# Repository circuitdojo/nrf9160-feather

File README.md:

# Circuit Dojo - nRF9160 Feather Hardware Files

## Purchase

Considering supporting the project and purchasing a nRF9160 Feather at the following locations:

1. [The Circuit Dojo Official Store](https://www.circuitdojo.com/products/nrf9160-feather)
2. [Digikey](https://www.digikey.com/en/products/detail/circuit-dojo/PASSY-NRF9160-FEATHER/13668137)

## Code

All code for this board can be [found here.](https://github.com/circuitdojo/nrf9160-feather-examples-and-drivers/tree/v1.9.x)

## Documentation

[Documentation is available here.](https://docs.circuitdojo.com)

## License

Hardware released under the CERN Open Hardware Licence Version 2 - Weakly Reciprocal. See **LICENSE.txt** for more info.

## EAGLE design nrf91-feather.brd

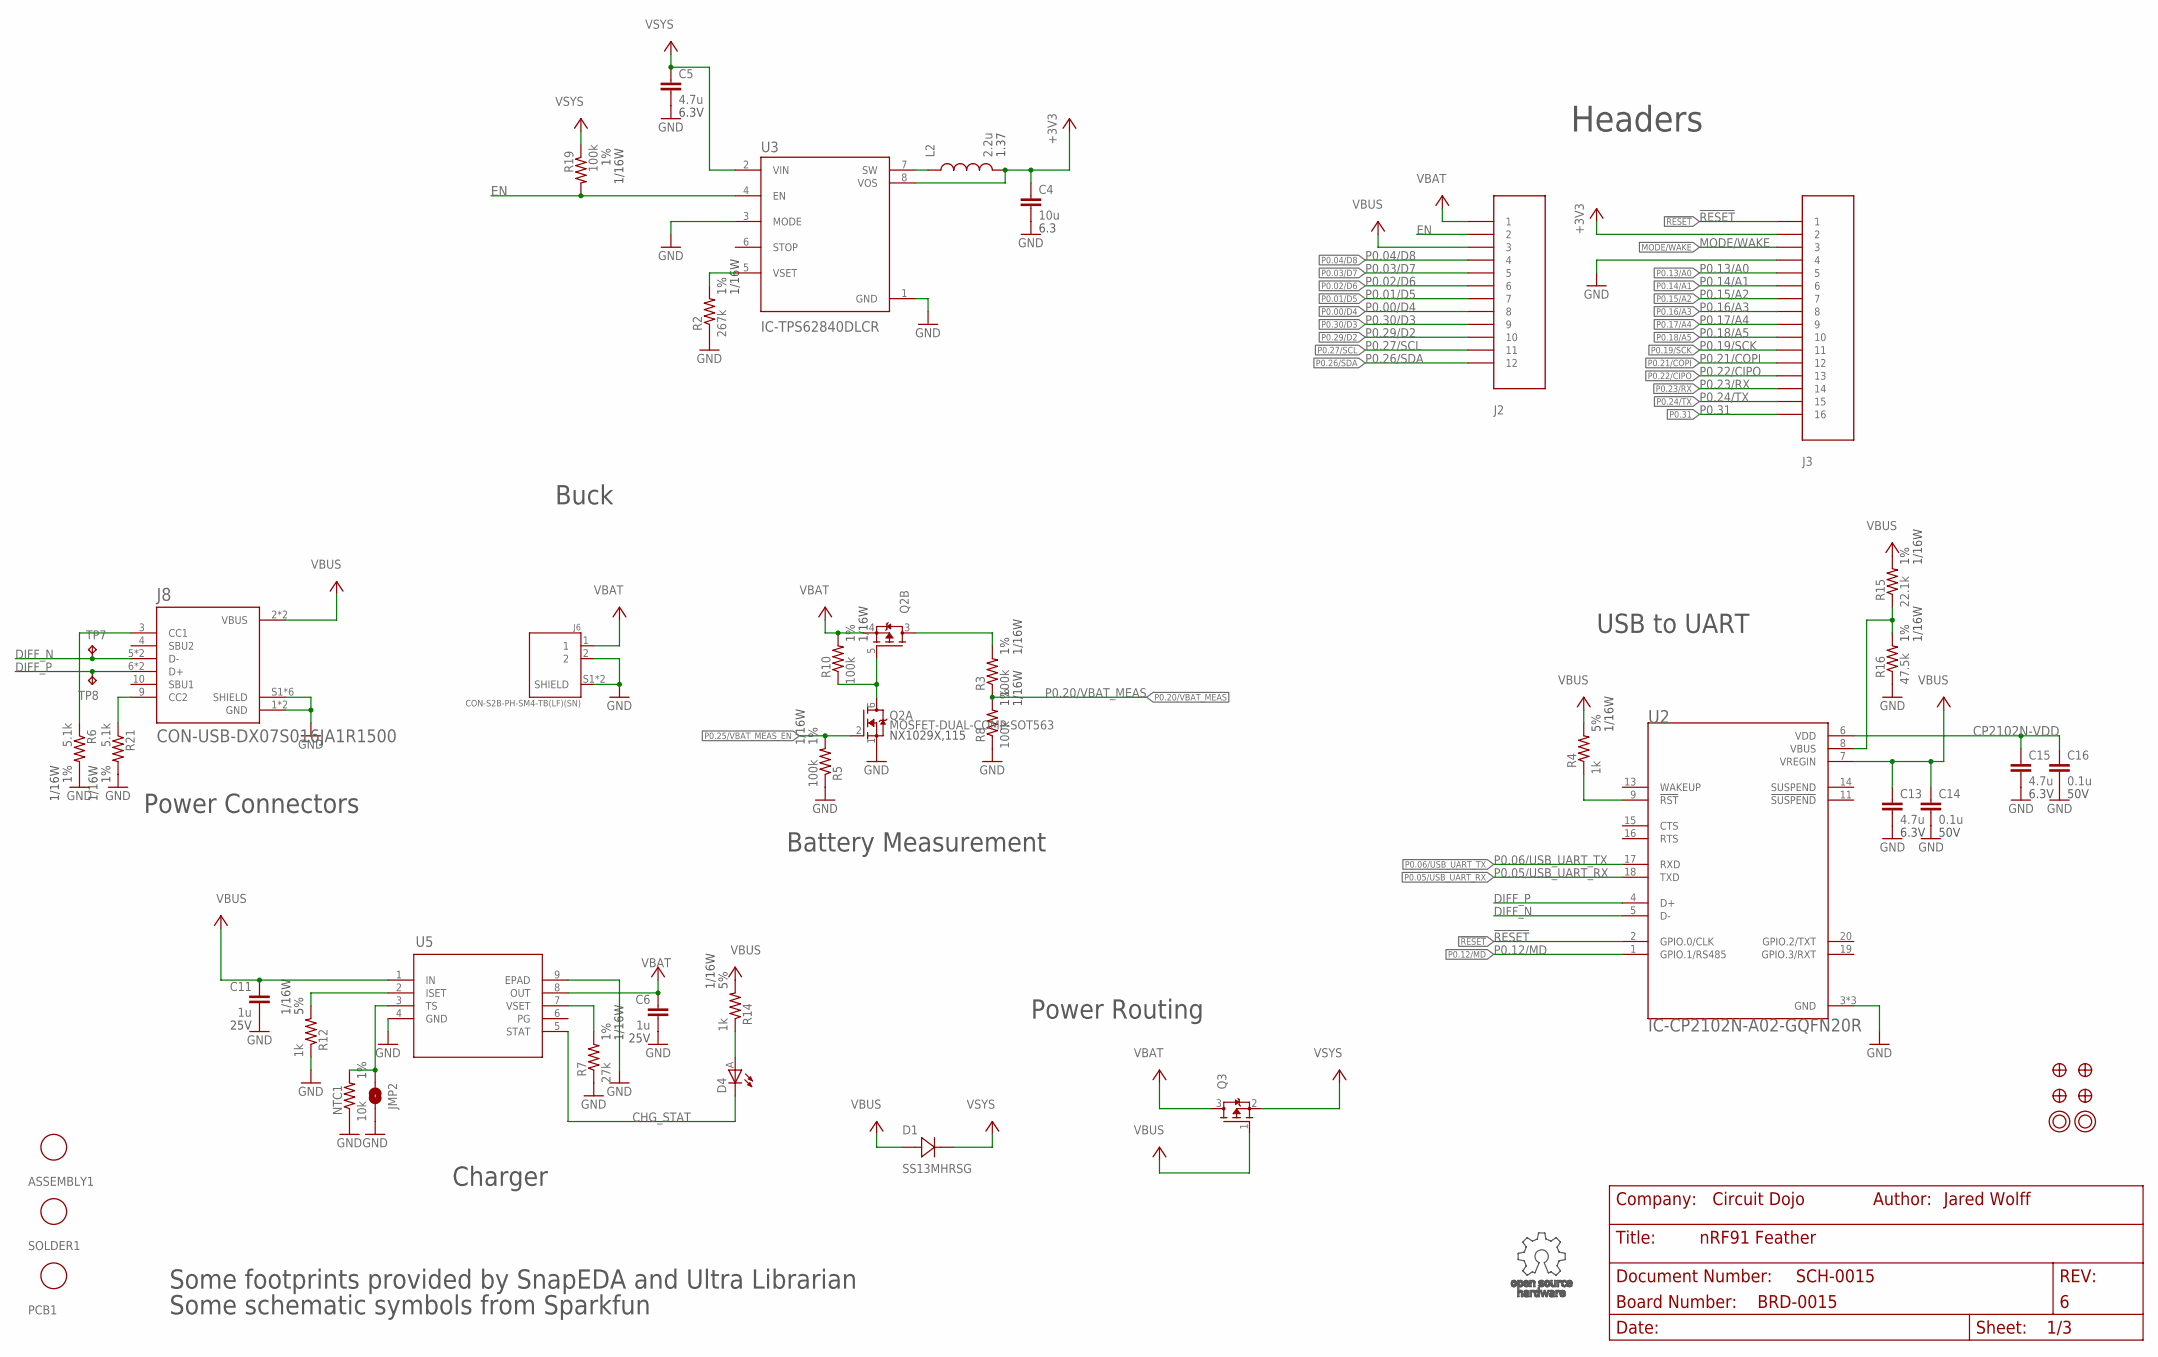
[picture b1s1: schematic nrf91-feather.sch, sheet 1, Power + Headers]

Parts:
ASSEMBLY1: ASSY-COST-NRF91-FEATHER; PLACEHOLDER
C4: 10u; C0603
C5, C13, C15: 4.7u; C0603
C6, C11: 1u; CAPC1005X55N
C14, C16: 0.1u; CAPC1005X55N
D1: DIO-SCHOTTKY-1A-SMA-MICRO; SMA-MICRO
D4: LED-ORANGE-0402; LED_EAST1005
J2: CON-HEADER-1X12-MALE-PIN
J3: CON-HEADER-1X16-MALE-PIN
J6: CON-S2B-PH-SM4-TB(LF)(SN); JST_S2B-PH-SM4-TB(LF)(SN)
J8: CON-USB-DX07S016JA1R1500; JAE_DX07S016JA1R1500
JMP2: JUMPER-NO-ROUND-NO; JUMPER-ROUND-N0
L2: 2.2u; IND-2P0X2P0X1P2
NTC1: 10k; R0402-M
PCB1: PCB-NRF91-FEATHER; PLACEHOLDER
Q2: MOSFET-DUAL-COMP-SOT563; SOT50P160X60-6N
Q3: MOSFET-P-20V-4.7A-SOT23; SOT23
R2: 267k; R0402-M
R3, R5, R8, R10, R19: 100k; R0402-M
R4, R12, R14: 1k; R0402-M
R6, R21: 5.1k; R0402-M
R7: 27k; R0402-M
R15: 22.1k; R0402-M
R16: 47.5k; R0402-M
SOLDER1: SOLDER-PASTE-ROOM-TEMP-50G; PLACEHOLDER
TP7, TP8: TP-1SIDE-1P0; TP-1P0
U2: IC-CP2102N-A02-GQFN20R; SILABS_CP2102N-A02-GQFN20R
U3: IC-TPS62840DLCR; SON50P200X150X100-8N
U5: IC-BQ25170JDSGR-WSON8; WSON8_BQ2517_TEX-L
U$3, U$4, U$34, U$35: FIDUCIAL-1MM
U$31, U$32: MOUNTING-HOLE-2.5MM-PLATED

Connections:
!RESET: J3.1, U2.2 (GPIO.0/CLK); also elsewhere on the board
+3V3: C4.1, J3.2, L2.P$2 (2), U3.8 (VOS); also elsewhere on the board
CHG_ISET: R12.2, U5.2 (ISET)
CHG_STAT: D4.C, U5.5 (STAT)
CHG_TS: JMP2.P$1 (1), NTC1.2, U5.3 (TS)
CHG_VSET: R7.2, U5.7 (VSET)
CP2102N-!RST: R4.1, U2.9 (!RST)
CP2102N-VDD: C15.1, C16.1, U2.6 (VDD)
DIFF_N: J8.5 (D-), J8.8 (D-), TP7.TP, U2.5 (D-)
DIFF_P: J8.6 (D+), J8.7 (D+), TP8.TP, U2.4 (D+)
EN: J2.2, R19.2, U3.4 (EN)
GND: C4.2, C5.2, C6.2, C11.2, C13.2, C14.2, C15.2, C16.2, J3.4, J6.2, J6.S1 (SHIELD), J6.S2 (SHIELD), J8.1 (GND), J8.12 (GND), J8.S1 (SHIELD), J8.S2 (SHIELD), J8.S3 (SHIELD), J8.S4 (SHIELD), J8.S5 (SHIELD), J8.S6 (SHIELD), JMP2.P$2 (2), NTC1.1, Q2.1 (S), R2.1, R5.1, R6.2, R7.1, R8.1, R12.1, R16.1, R21.2, U2.3 (GND), U2.12 (GND), U2.21 (GND), U3.1 (GND), U3.3 (MODE), U5.4 (GND), U5.9 (EPAD); also elsewhere on the board
MODE/WAKE: J3.3; also elsewhere on the board
unnamed: R2.2, U3.5 (VSET)
unnamed: L2.P$1 (1), U3.7 (SW)
unnamed: Q2.3 (D), R3.2
unnamed: Q2.5 (G), Q2.6 (D), R10.1
unnamed: R15.1, R16.2, U2.8 (VBUS)
unnamed: D4.A, R14.1
P0.00/D4: J2.8; also elsewhere on the board
P0.01/D5: J2.7; also elsewhere on the board
P0.02/D6: J2.6; also elsewhere on the board
P0.03/D7: J2.5; also elsewhere on the board
P0.04/D8: J2.4; also elsewhere on the board
P0.05/USB_UART_RX: U2.18 (TXD); also elsewhere on the board
P0.06/USB_UART_TX: U2.17 (RXD); also elsewhere on the board
P0.12/MD: U2.1 (GPIO.1/RS485); also elsewhere on the board
P0.13/A0: J3.5; also elsewhere on the board
P0.14/A1: J3.6; also elsewhere on the board
P0.15/A2: J3.7; also elsewhere on the board
P0.16/A3: J3.8; also elsewhere on the board
P0.17/A4: J3.9; also elsewhere on the board
P0.18/A5: J3.10; also elsewhere on the board
P0.19/SCK: J3.11; also elsewhere on the board
P0.20/VBAT_MEAS: R3.1, R8.2; also elsewhere on the board
P0.21/COPI: J3.12; also elsewhere on the board
P0.22/CIPO: J3.13; also elsewhere on the board
P0.23/RX: J3.14; also elsewhere on the board
P0.24/TX: J3.15; also elsewhere on the board
P0.25/VBAT_MEAS_EN: Q2.2 (G), R5.2; also elsewhere on the board
P0.26/SDA: J2.12; also elsewhere on the board
P0.27/SCL: J2.11; also elsewhere on the board
P0.29/D2: J2.10; also elsewhere on the board
P0.30/D3: J2.9; also elsewhere on the board
P0.31: J3.16; also elsewhere on the board
USB_CC1: J8.3 (CC1), R6.1
USB_CC2: J8.9 (CC2), R21.1
VBAT: C6.1, J2.1, J6.1, Q2.4 (S), Q3.3 (D), R10.2, U5.8 (OUT)
VBUS: C11.1, C13.1, C14.1, D1.2 (1), J2.3, J8.2 (VBUS), J8.11 (VBUS), Q3.1 (G), R4.2, R14.2, R15.2, U2.7 (VREGIN), U5.1 (IN)
VSYS: C5.1, D1.1 (2), Q3.2 (S), R19.1, U3.2 (VIN); also elsewhere on the board

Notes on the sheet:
Headers
Some footprints provided by SnapEDA and Ultra Librarian
Buck
Power Routing
Battery Measurement
Charger
USB to UART
Power Connectors
Some schematic symbols from Sparkfun

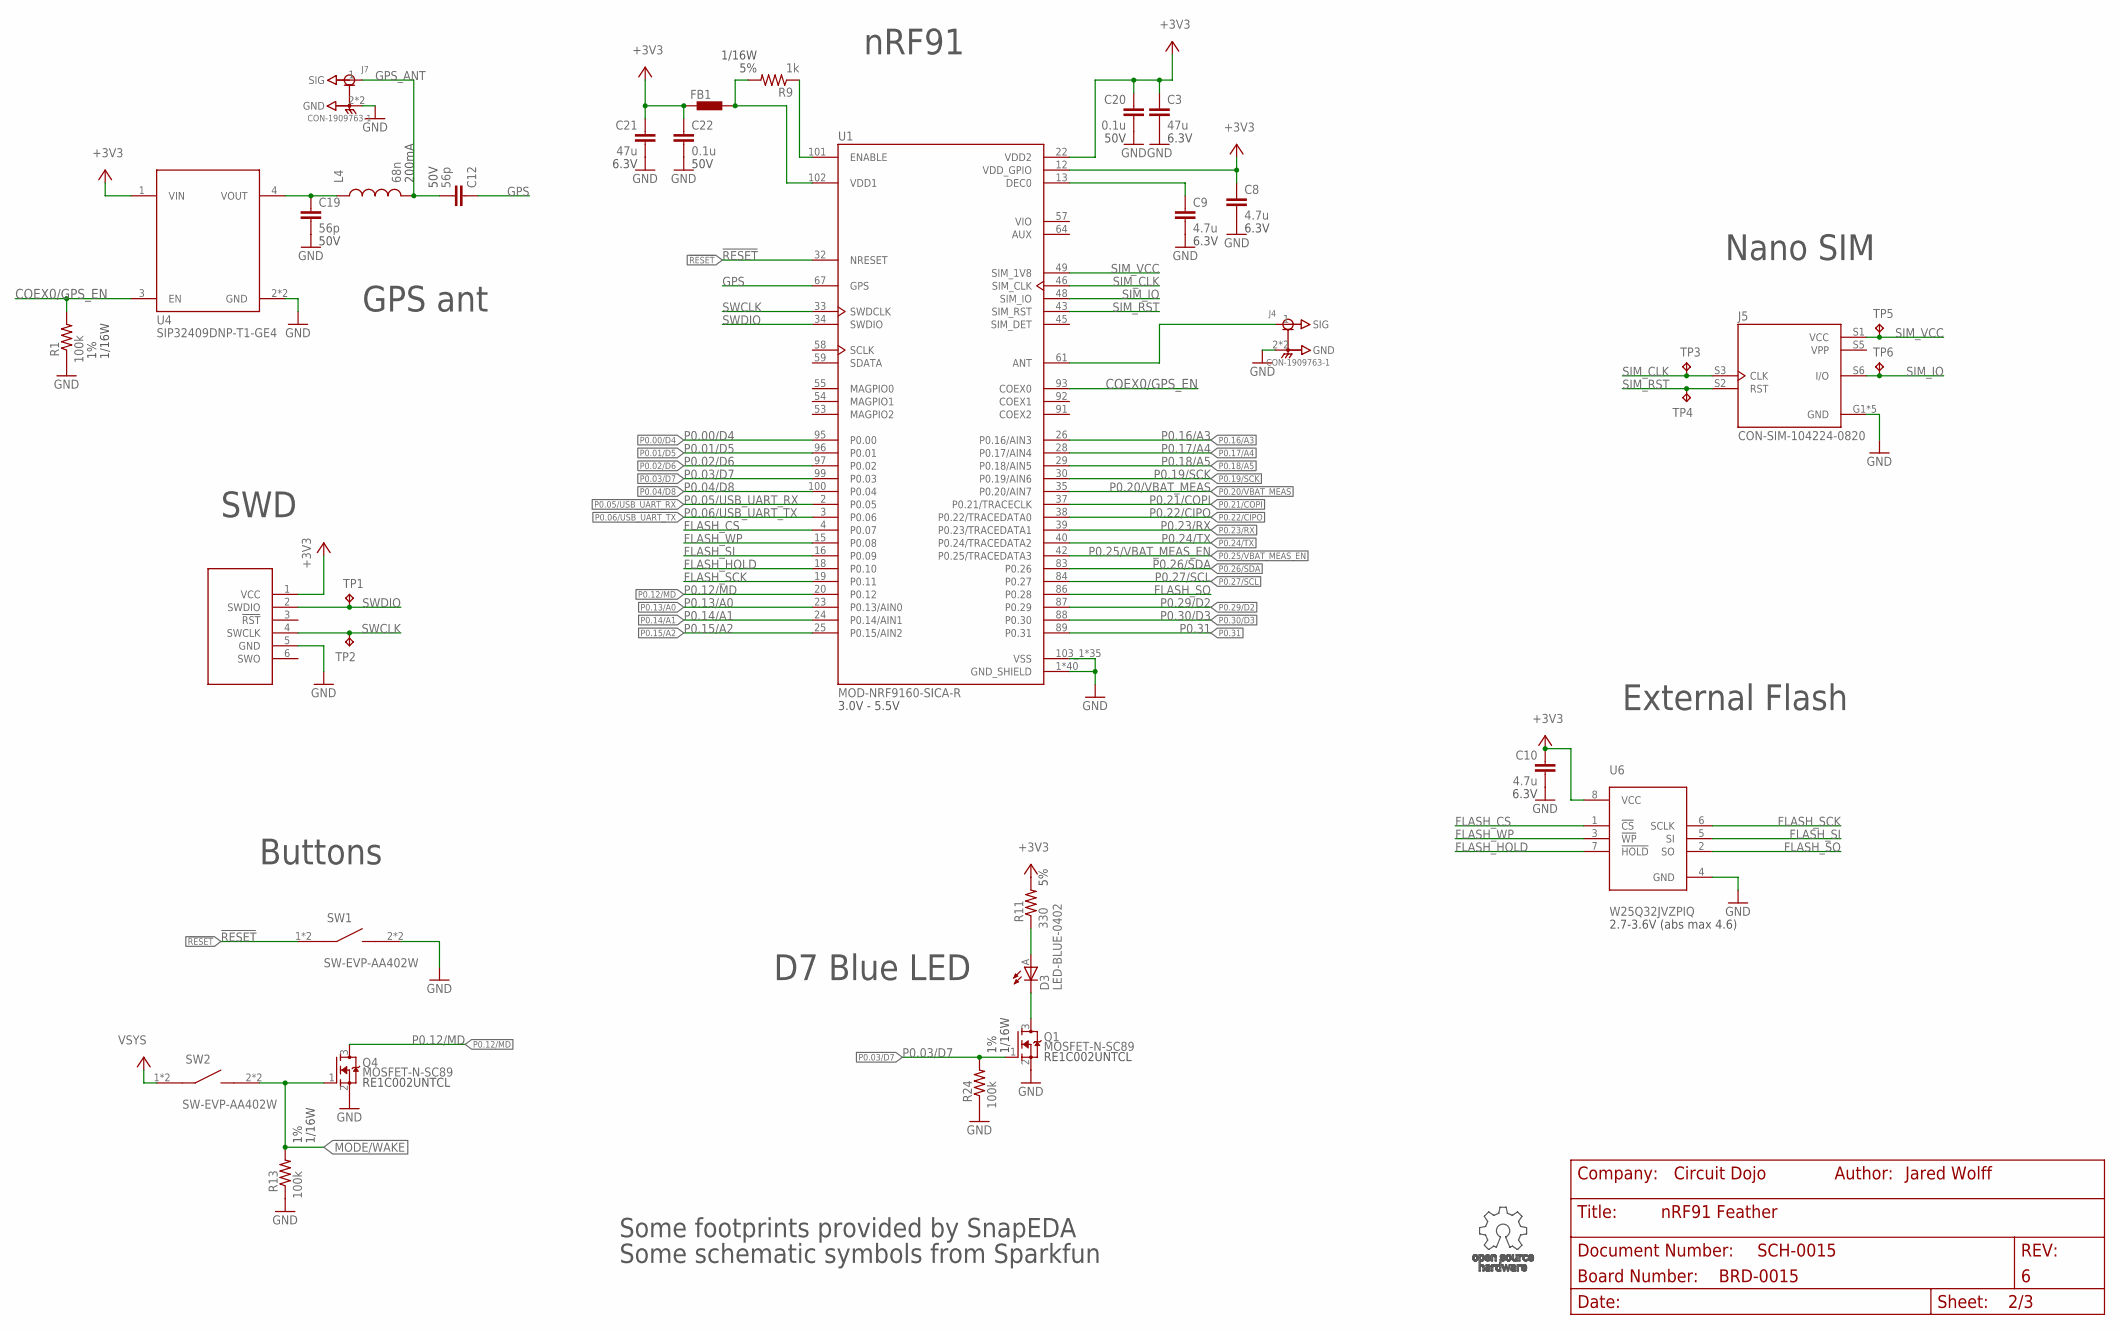
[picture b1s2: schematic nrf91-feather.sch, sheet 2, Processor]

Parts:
C3, C21: 47u; C0805
C8, C9, C10: 4.7u; C0603
C12, C19: 56p; CAPC1005X55N
C20, C22: 0.1u; CAPC1005X55N
D3: LED-BLUE-0402; LED_EAST1005
FB1: FERRITE-120-100MHZ-0402; R0402-M
J4, J7: CON-1909763-1; TE_1909763-1
J5: CON-SIM-104224-0820; MOLEX_104224-0820
J9: CON-TC2030-MCP-NL; TC2030-MCP-NL
L4: 68n; IND0402_22N_TAI
Q1, Q4: MOSFET-N-SC89; DIO_RB558WMF-L
R1, R13, R24: 100k; R0402-M
R9: 1k; R0402-M
R11: 330; R0402-M
SW1, SW2: SW-EVP-AA402W
TP1, TP2, TP3, TP4, TP5, TP6: TP-1SIDE-1P0; TP-1P0
U1: MOD-NRF9160-SICA-R; NORDIC_NRF9160-SICA-R
U4: POWER-SWITCH-SIP32409-DFN4; SON50P160X120X60-5N
U6: FLASH-W25Q32JVZPIQ-WSON; WIN_ZP-8-L

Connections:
!RESET: SW1.1, SW1.3 (1), U1.32 (NRESET); also elsewhere on the board
+3V3: C3.1, C8.1, C10.1, C20.1, C21.1, C22.1, FB1.1, J9.1 (VCC), R11.2, U1.12 (VDD_GPIO), U1.22 (VDD2), U4.1 (VIN), U6.8 (VCC); also elsewhere on the board
ANT: J4.1 (SIG), U1.61 (ANT)
COEX0/GPS_EN: R1.2, U1.93 (COEX0), U4.3 (EN)
FLASH_CS: U1.4 (P0.07), U6.1 (!CS)
FLASH_HOLD: U1.18 (P0.10), U6.7 (!HOLD)
FLASH_SCK: U1.19 (P0.11), U6.6 (SCLK)
FLASH_SI: U1.16 (P0.09), U6.5 (SI)
FLASH_SO: U1.86 (P0.28), U6.2 (SO)
FLASH_WP: U1.15 (P0.08), U6.3 (!WP)
GND: C3.2, C8.2, C9.2, C10.2, C19.2, C20.2, C21.2, C22.2, J4.2 (GND), J4.3 (GND), J5.G1 (GND), J5.G2 (GND), J5.G3 (GND), J5.G4 (GND), J5.S4 (GND), J7.2 (GND), J7.3 (GND), J9.5 (GND), Q1.2 (S), Q4.2 (S), R1.1, R13.1, R24.1, SW1.2, SW1.4 (2), U1.1 (GND_SHIELD), U1.5 (GND_SHIELD), U1.6 (GND_SHIELD), U1.7 (GND_SHIELD), U1.8 (GND_SHIELD), U1.9 (GND_SHIELD), U1.11 (GND_SHIELD), U1.14 (GND_SHIELD), U1.17 (GND_SHIELD), U1.21 (GND_SHIELD), U1.27 (GND_SHIELD), U1.31 (GND_SHIELD), U1.36 (GND_SHIELD), U1.41 (GND_SHIELD), U1.44 (GND_SHIELD), U1.47 (GND_SHIELD), U1.50 (GND_SHIELD), U1.52 (GND_SHIELD), U1.56 (GND_SHIELD), U1.60 (GND_SHIELD), U1.62 (GND_SHIELD), U1.63 (GND_SHIELD), U1.65 (GND_SHIELD), U1.66 (GND_SHIELD), U1.68 (GND_SHIELD), U1.69 (GND_SHIELD), U1.72 (GND_SHIELD), U1.74 (GND_SHIELD), U1.75 (GND_SHIELD), U1.76 (GND_SHIELD), U1.77 (GND_SHIELD), U1.78 (GND_SHIELD), U1.79 (GND_SHIELD), U1.80 (GND_SHIELD), U1.81 (GND_SHIELD), U1.82 (GND_SHIELD), U1.85 (GND_SHIELD), U1.90 (GND_SHIELD), U1.94 (GND_SHIELD), U1.98 (GND_SHIELD), U1.103_1 (VSS), U1.103_2 (VSS), U1.103_3 (VSS), U1.103_4 (VSS), U1.103_5 (VSS), U1.103_6 (VSS), U1.103_7 (VSS), U1.103_8 (VSS), U1.103_9 (VSS), U1.103_10 (VSS), U1.103_11 (VSS), U1.103_12 (VSS), U1.103_13 (VSS), U1.103_14 (VSS), U1.103_15 (VSS), U1.103_16 (VSS), U1.103_17 (VSS), U1.103_18 (VSS), U1.103_19 (VSS), U1.103_20 (VSS), U1.103_21 (VSS), U1.103_22 (VSS), U1.103_23 (VSS), U1.103_24 (VSS), U1.103_25 (VSS), U1.103_26 (VSS), U1.103_27 (VSS), U1.103_28 (VSS), U1.103_29 (VSS), U1.103_30 (VSS), U1.103_31 (VSS), U1.103_32 (VSS), U1.103_33 (VSS), U1.103_34 (VSS), U1.103_35 (VSS), U4.2 (GND), U4.5 (GND), U6.4 (GND); also elsewhere on the board
GPS: C12.1, U1.67 (GPS)
GPS_ANT: C12.2, J7.1 (SIG), L4.2
LNA_SW_OUT: C19.1, L4.1, U4.4 (VOUT)
MODE/WAKE: Q4.1 (G), R13.2, SW2.2, SW2.4 (2); also elsewhere on the board
unnamed: R9.1, U1.101 (ENABLE)
unnamed: C9.1, U1.13 (DEC0)
unnamed: D3.A, R11.1
unnamed: D3.C, Q1.3 (D)
unnamed: FB1.2, R9.2, U1.102 (VDD1)
P0.00/D4: U1.95 (P0.00); also elsewhere on the board
P0.01/D5: U1.96 (P0.01); also elsewhere on the board
P0.02/D6: U1.97 (P0.02); also elsewhere on the board
P0.03/D7: Q1.1 (G), R24.2, U1.99 (P0.03); also elsewhere on the board
P0.04/D8: U1.100 (P0.04); also elsewhere on the board
P0.05/USB_UART_RX: U1.2 (P0.05); also elsewhere on the board
P0.06/USB_UART_TX: U1.3 (P0.06); also elsewhere on the board
P0.12/MD: Q4.3 (D), U1.20 (P0.12); also elsewhere on the board
P0.13/A0: U1.23 (P0.13/AIN0); also elsewhere on the board
P0.14/A1: U1.24 (P0.14/AIN1); also elsewhere on the board
P0.15/A2: U1.25 (P0.15/AIN2); also elsewhere on the board
P0.16/A3: U1.26 (P0.16/AIN3); also elsewhere on the board
P0.17/A4: U1.28 (P0.17/AIN4); also elsewhere on the board
P0.18/A5: U1.29 (P0.18/AIN5); also elsewhere on the board
P0.19/SCK: U1.30 (P0.19/AIN6); also elsewhere on the board
P0.20/VBAT_MEAS: U1.35 (P0.20/AIN7); also elsewhere on the board
P0.21/COPI: U1.37 (P0.21/TRACECLK); also elsewhere on the board
P0.22/CIPO: U1.38 (P0.22/TRACEDATA0); also elsewhere on the board
P0.23/RX: U1.39 (P0.23/TRACEDATA1); also elsewhere on the board
P0.24/TX: U1.40 (P0.24/TRACEDATA2); also elsewhere on the board
P0.25/VBAT_MEAS_EN: U1.42 (P0.25/TRACEDATA3); also elsewhere on the board
P0.26/SDA: U1.83 (P0.26); also elsewhere on the board
P0.27/SCL: U1.84 (P0.27); also elsewhere on the board
P0.29/D2: U1.87 (P0.29); also elsewhere on the board
P0.30/D3: U1.88 (P0.30); also elsewhere on the board
P0.31: U1.89 (P0.31); also elsewhere on the board
SIM_CLK: J5.S3 (CLK), TP3.TP, U1.46 (SIM_CLK)
SIM_IO: J5.S6 (I/O), TP6.TP, U1.48 (SIM_IO)
SIM_RST: J5.S2 (RST), TP4.TP, U1.43 (SIM_RST)
SIM_VCC: J5.S1 (VCC), TP5.TP, U1.49 (SIM_1V8)
SWCLK: J9.4 (SWCLK), TP2.TP, U1.33 (SWDCLK)
SWDIO: J9.2 (SWDIO), TP1.TP, U1.34 (SWDIO)
VIO: U1.57 (VIO)
VPP: J5.S5 (VPP)
VSYS: SW2.1, SW2.3 (1); also elsewhere on the board

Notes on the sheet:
nRF91
Nano SIM
SWD
Buttons
External Flash
D7 Blue LED
3.0V - 5.5V
2.7-3.6V (abs max 4.6)
GPS ant
Some footprints provided by SnapEDA
Some schematic symbols from Sparkfun

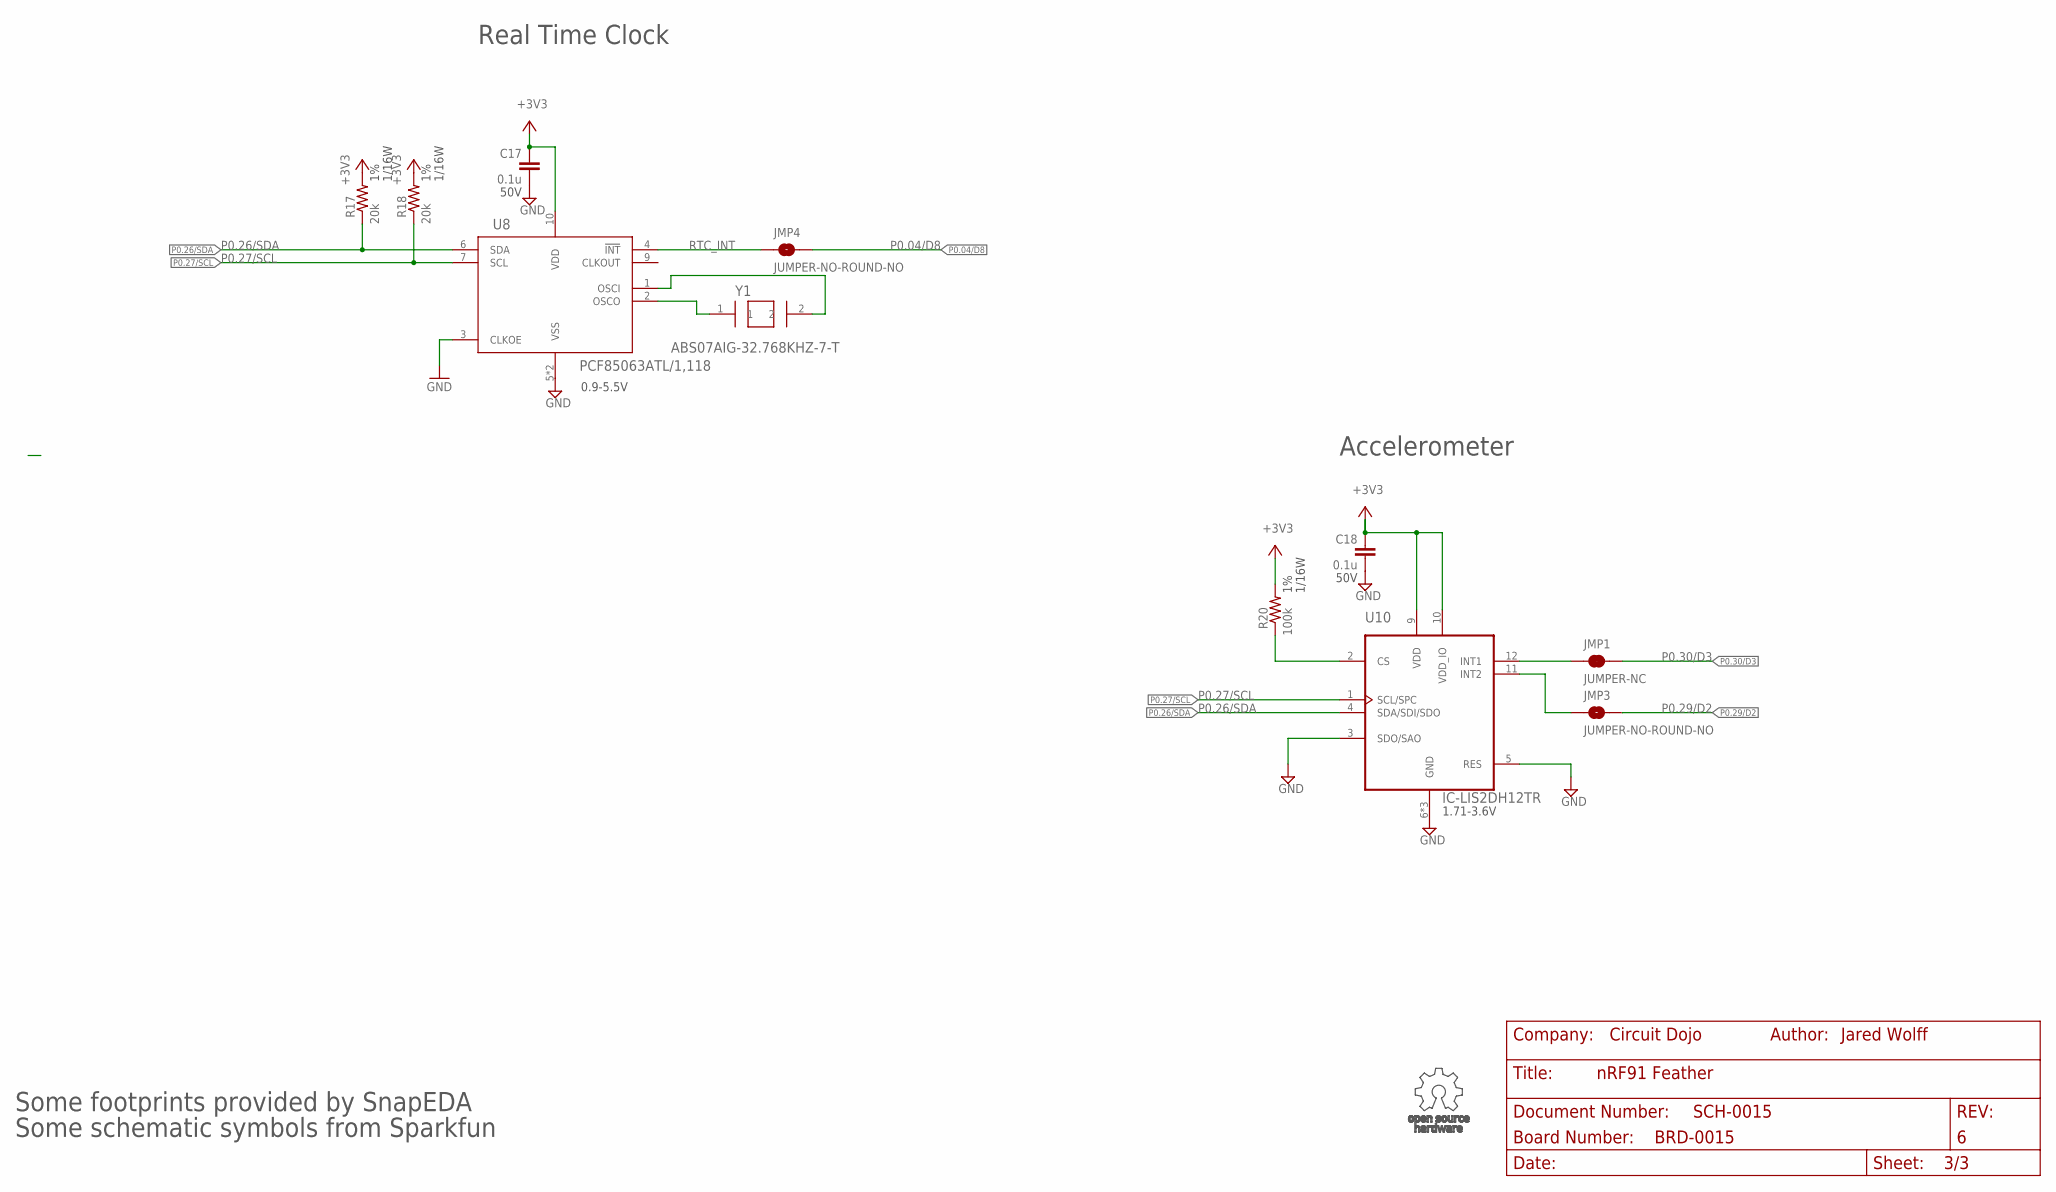
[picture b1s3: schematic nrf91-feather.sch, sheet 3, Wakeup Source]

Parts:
C17, C18: 0.1u; CAPC1005X55N
JMP1: JUMPER-NC; JUMPER-ROUND-NC
JMP3, JMP4: JUMPER-NO-ROUND-NO; JUMPER-ROUND-N0
R17, R18: 20k; R0402-M
R20: 100k; R0402-M
U8: IC-PCF85063ATL/1; DFN10_2P7X2P7-L
U10: IC-LIS2DH12TR; PQFN50P200X200100-12N
Y1: XTAL-ABS07AIG-32.768KHZ-7-T; XTAL320X150X90

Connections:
+3V3: C17.1, C18.1, R17.2, R18.2, R20.2, U8.10 (VDD), U10.9 (VDD), U10.10 (VDD_IO); also elsewhere on the board
GND: C17.2, C18.2, U8.3 (CLKOE), U8.5 (VSS), U8.11 (VSS), U10.3 (SDO/SAO), U10.5 (RES), U10.6 (GND), U10.7 (GND), U10.8 (GND); also elsewhere on the board
LIS2DH_INT1: JMP1.P$1 (1), U10.12 (INT1)
LIS2DH_INT2: JMP3.P$1 (1), U10.11 (INT2)
unnamed: R20.1, U10.2 (CS)
unnamed: U8.1 (OSCI), Y1.2
unnamed: U8.2 (OSCO), Y1.1
P0.04/D8: JMP4.P$2 (2); also elsewhere on the board
P0.26/SDA: R17.1, U8.6 (SDA), U10.4 (SDA/SDI/SDO); also elsewhere on the board
P0.27/SCL: R18.1, U8.7 (SCL), U10.1 (SCL/SPC); also elsewhere on the board
P0.29/D2: JMP3.P$2 (2); also elsewhere on the board
P0.30/D3: JMP1.P$2 (2); also elsewhere on the board
RTC_INT: JMP4.P$1 (1), U8.4 (!INT)

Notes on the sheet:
Real Time Clock
0.9-5.5V
Accelerometer
1.71-3.6V
Some footprints provided by SnapEDA
Some schematic symbols from Sparkfun

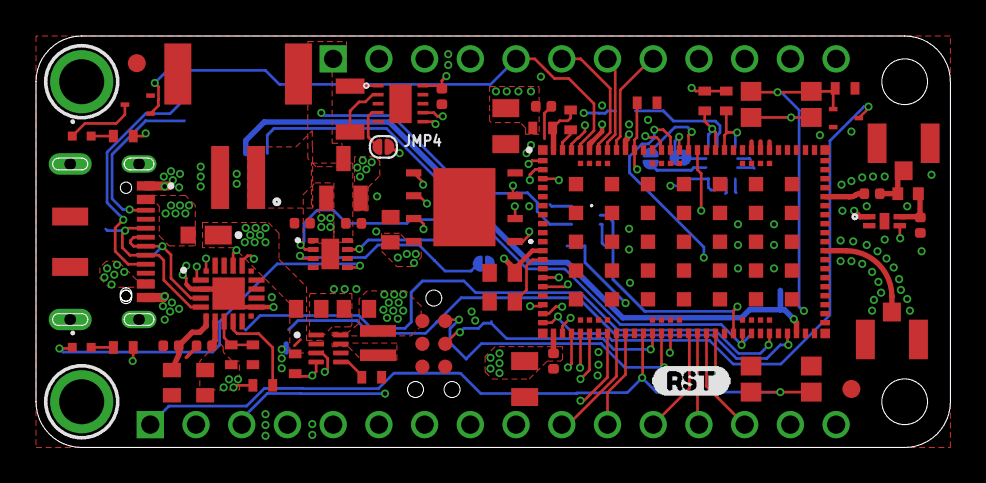
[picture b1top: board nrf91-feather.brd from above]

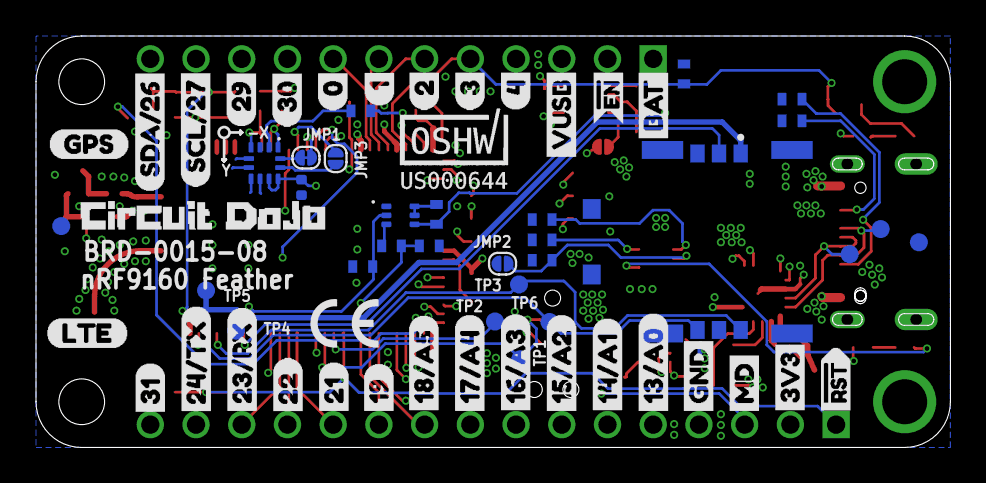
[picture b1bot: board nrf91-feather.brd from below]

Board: 4 copper layers, 50.8 x 22.9 mm, 127 parts (61 on the bottom side), 78 nets.

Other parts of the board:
U$1: 13#A00
U$2: LOGO-CIRCUITDOJO
U$5: A3L-LOC
U$6: LOGO-OSHWA
U$7: LOGO-CE
U$8: 290
U$9: BAT0
U$10: 20
U$11: 30
U$12: 310
U$13: 00
U$14: MD0
U$15: #RST0
U$16: 24#TX0
U$17: 23#RX0
U$18: 220
U$19: 210
U$20: 190
U$21: GPS0
U$22: LTE0
U$23: RST0
U$24: 10
U$25: #EN0
U$26: SCL#270
U$27: SDA#260
U$28: 300
U$39: 14#A10
U$40: 15#A20
U$41: 16#A30
U$42: 17#A40
U$43: 18#A50
U$69: GND12
U$71: 3V314
U$73: VUSB25
U$89: 412

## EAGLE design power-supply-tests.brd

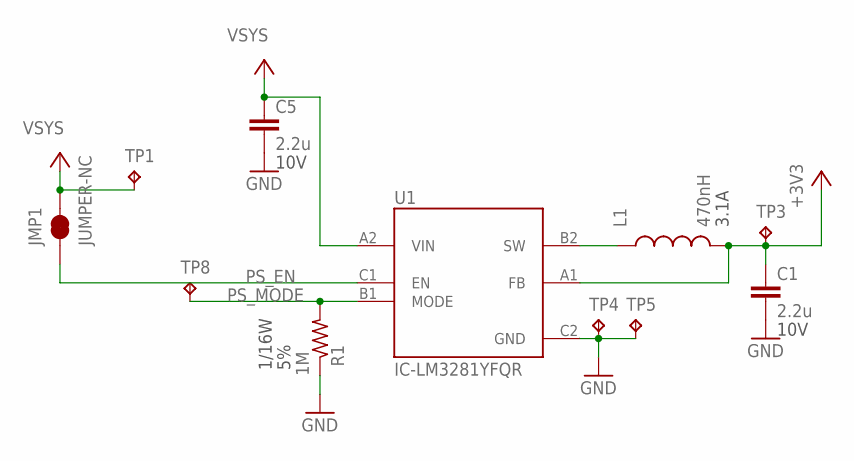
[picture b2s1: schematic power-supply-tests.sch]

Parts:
C1, C5: 2.2u; C0603
JMP1: JUMPER-NC; JUMPER-ROUND-NC
L1: 470nH; INDC2012X100N
R1: 1M; R0402-M
TP1, TP3, TP4, TP5, TP8: HEADER-1; CON-HEADER-1X1-POGO-1P9
U1: IC-LM3281YFQR; BGA6N40P2X3_116X143X67N

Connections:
+3V3: C1.1, L1.2, TP3.1, U1.A1 (FB)
GND: C1.2, C5.2, R1.1, TP4.1, TP5.1, U1.C2 (GND)
PS_EN: JMP1.P$1 (1), U1.C1 (EN)
PS_MODE: R1.2, TP8.1, U1.B1 (MODE)
PS_SW1: L1.1, U1.B2 (SW)
VSYS: C5.1, JMP1.P$2 (2), TP1.1, U1.A2 (VIN)

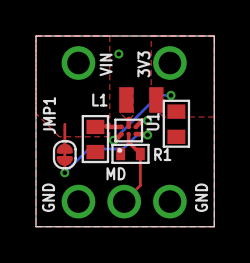
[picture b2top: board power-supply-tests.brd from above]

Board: 2 copper layers, 9.9 x 10.6 mm, 11 parts (0 on the bottom side), 6 nets.

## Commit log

2020-04-29 First commit. This board went to fab.
2020-04-29 Adding parallel LDO for low power op. (without need to shut everything off)
2020-05-05 Current tweaks
2020-05-07 Removing LDO. Cleaning up traces. Fixing slot issue! Adding timer back.
2020-05-07 1. Add doc outline 2. Adding tdocu 3. Exporting assembly docs using cam2print PDF 4. Updating nRF91 footprint
2020-05-11 1. Clean up silk 2. Updated 3D packages 3. Pushed to OSH Park + Fusion 4. Added 1.8V LDO for LNA
    Proto2
2020-05-20 1. Changing name of design to nRF9160 Feather 2. Fixing holes with BOM export.
2020-05-26 1. Adding pulldown on EN pin
2020-06-08 Using internal switch to route GPS signal.
2020-06-08 Circuitry for external active GPS antenna.
2020-06-30 Replacing some parts that are not available. Renaming MOSI to COPI, MISO to CIPO
2020-06-30 Adding LICENSE file. Adding STEP file.
2020-06-30 Adding image of nRF9160 Feather.
2020-07-02 Ignoring project files.
2020-07-03 Test points for SWD. Adding indent and removing solder pads from underneath the USB connector. Connecting un-connected ground connections Re-arranging bypass/GPS circuit
2020-07-17 Adding OSHW logo with project #.
2020-07-18 Replacing 47u with JMK212BJ476MG-T Replacing 56pf with CC0402GRNPO9BN560 Replace 4.7u with JMK107BB7475MA-T
2020-07-26 Adding PDF schematic.
2020-07-31 Fixing silkscreen for a few components.
2020-08-27 Adding CE marking
2020-09-23 V2 edits.
    * Replace battery measurement load switch
    * Fix footprint for LEDs
2020-10-19 Adding LIS2DH12TR Changing mode pin to be post switch, pre-GPIO Adding more clear pins labels. (Thanks to Sparkfun Buzzard - https://sparkfunx.github.io/Buzzard/)
2020-10-27 Adding jumper for "permanent on" if the end user wants it.
2020-10-30 Fixing orientation of XY label
2020-12-02 Fixing SDA/SCL labels
2020-12-07 Updating LIS2DH footprint for assembly drawing.
2021-01-14 Adding test points to SIM related signals
2021-01-14 Updating PDF and step file
2021-02-02 Updating thermal pad for U8 and U3. Reducing aperture to 60% of the pad size.
2021-02-02 Updated nRF9160 Footprint based on factory feedback and Sparkfun's changes.
2021-05-11 Adding accelerometer INT2 pin connection.
2021-06-26 Optimizing power layout
    Changed:
    * Created large power paths on middle layers (power an return)
    * Pin7 on power supply chip to ground (power save mode/pfm enabled)
2021-06-26 Replacing U4 with 2.8V regulator.
    Changed:
    * U4 to MIC5365-2.8YC5-TR
2021-06-26 Comparing and fixing U3 connections
    Changed:
    * U3.8 should not be connected to VSYS. Now the same as a few reference designs i've seen.
2021-06-26 Undo changing U4 to LDO. Needs to stay as a load switch.
    Changed:
    * U4 back to the original part.
2021-07-09 Changes for next revision of the nRF9160 Feather
    Removed:
    * TVS diode
    Changed:
    * USB is now USB-C
    * Power supply is now Boost + LDO combo (not final)
    * LED position due to USB-C being larger
2021-07-17 Changed up power supply as the Torex part will not work. :(
    Changed:
    * Power supply to LM3281
    * Cleaned up solder mask/paste mask for USB
    * Removed paste mask for jumper
    Added:
    * Connection for enable pin to P0.13
2021-07-17 Power supply test board with Torex part
    Added:
    * brd and sch
2021-07-26 Latest changes to nRF91
    Changed:
    * Power supply inductor
    * Power supply tests board updated
2021-07-26 Fixing inner layer
    Changed:
    * 3v3 internal layer needs some copper around slots so it doesn't short.
2021-07-27 Changing from pull-down to pull-up on mode pin of LM3281
    Changed:
    * R7 is now a pull-up to VSYS
2021-07-29 Updating charger part.
    Changed:
    * Updated schematic and layout to replace the ST part with a MCP part
2021-07-29 Updating 0,0 for schottky diodes
    Updated:
    * Repositioned center point of diodes for PNP
2021-09-03 Clean up.
    Changed:
    * Named some unnamed nets
    * Changed LNA_EN to GPS_EN
    * R7 connects to 3.3V instead of VSYS
2021-09-08 Pushing 3d changes to Fusion360
    Changed
    * Fixed schottky diode 3d package placement
    * Updating versions of footprints
2022-04-08 Updates for v5. Always-on operation.
    Removed:
    * 5V pin is now direct connect to USB connector (removed schottky)
    Changed:
    * Changed 47uf cap to 4.7u for B1 variant
    * Replaced Buck with TPS62840
    * Added jumper for disabling charger
2022-04-08 Cleaning up
    Removed:
    * Reference designators
2022-04-08 Converting pin labels to Nordic specific pins
    Changed:
    * Pins now reflect the ports they're connected to.
2022-04-14 Ground fill near buck is modified
    Changed:
    * Removed thermals from ground fill near U3
2022-04-14 Minor clean up
    Changed:
    * Bottom layer trace/ground fix
2022-04-14 Updating documentation to v4
    Changed:
    * v4 brd and sch
    * Updated schematic pdf
2022-04-16 Cleanup
    Changed:
    * Improving ground paths
2022-06-06 V5 Proto 1
2022-06-27 Modifications
2022-07-21 Updating step file
    Changed:
    * Updated to v4 design
2022-07-31 Updating use of WP and HOLD pins
    Changed
    * Removed connections directly to mcu and replaced with pull-ups
2022-08-01 Adding updated bypass and filtering for power supply
    Changed:
    * Ferrite and 47u for power inputs
    * Re-routed battery measurement circuit
    * Cleaned up
2022-08-01 Reconnect flash signals
    Changed:
    * Reconnect WP and HOLD signls
2022-08-01 Consolidating parts
    Changed:
    * R9 to 1k
2022-08-01 Silkscreen tweaks
    Changed:
    * Analog pins now have analog names (again)
2022-10-24 Minor tweaks for production
    Changed
    * Fixed parts that don't have a tDocu reference designator
2022-10-24 Updating documentation
    Changed:
    * Updated schematic
    * Updated Readme
    * Updated step file
    * Update image of board
2022-10-24 Update to Version 5
    * No longer supports complete shutdown mode
    * Using nRF9160 B1A variant
    * Now supports "buttonless" DFU mode
    * Now supports direct USB-C connection
    Added:
    * Ferrite and 47u for power inputs
2023-01-03 Rename zFUNDING.yml to FUNDING.yml
2023-09-05 Fixed Iq issues when Vbat > 3.8V
    Changed:
    Connected RTC directly to 3.3V
2024-01-29 Addressing issue with paste mask on U8
2024-05-22 Updating design:
    - Removing all surrounding silkscreen for AOI
    - Update board version #
2024-05-22 Updating STEP file.
2024-05-22 Pushing v6 files.
2024-05-22 Updating readme
2024-07-09 Release changes
    - Updating readme
    - Updaitng Rev # in schematic
2024-11-30 Adding USB test points.
2025-01-23 Adding v7/v8 schematic

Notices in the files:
parts and their libraries:
wolff-den: ©2009 ROFA.cz - modified and updated by Robert Darlington ‹rdarlington@gmail.com›
COPYRIGHT: Copyright (C) 2022 Ultra Librarian. All rights reserved.
